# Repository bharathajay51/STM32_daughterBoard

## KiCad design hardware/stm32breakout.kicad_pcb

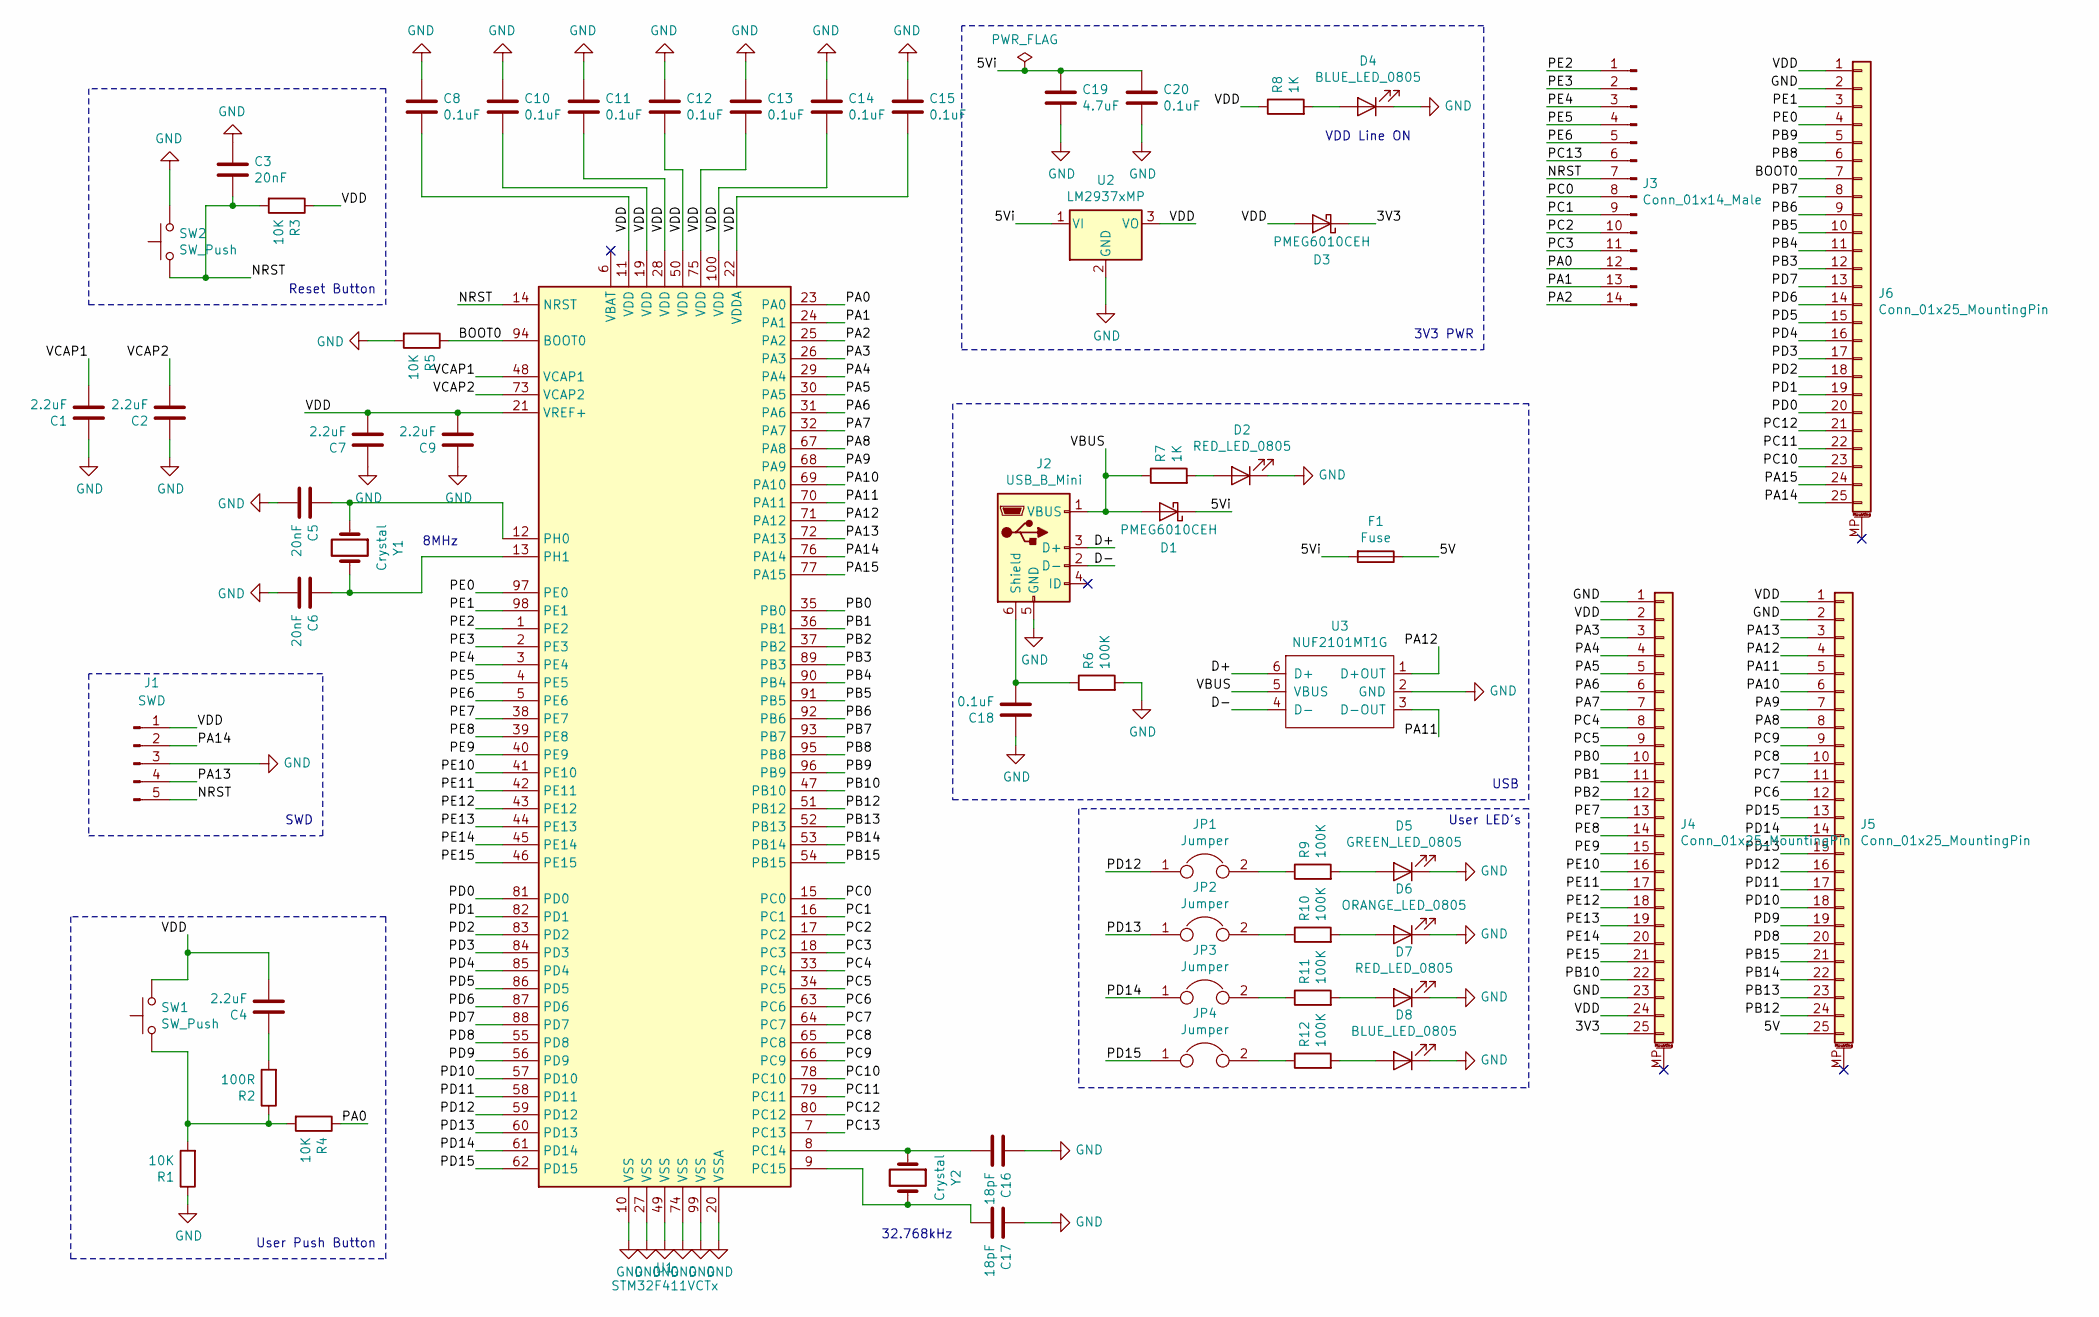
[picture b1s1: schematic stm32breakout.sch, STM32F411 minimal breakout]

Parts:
C1, C2, C4, C7, C9: 2.2uF; C_0805_2012Metric_Pad1.15x1.40mm_HandSolder
C3, C5, C6: 20nF; C_0805_2012Metric_Pad1.15x1.40mm_HandSolder
C8, C10, C11, C12, C13, C14, C15, C18, C20: 0.1uF; C_0805_2012Metric_Pad1.15x1.40mm_HandSolder
C16, C17: 18pF; C_0805_2012Metric_Pad1.15x1.40mm_HandSolder
C19: 4.7uF; C_0805_2012Metric_Pad1.15x1.40mm_HandSolder
D1, D3: PMEG6010CEH; D_SOD-123
D2, D7: RED_LED_0805; LED_0805_2012Metric_Pad1.15x1.40mm_HandSolder
D4, D8: BLUE_LED_0805; LED_0805_2012Metric_Pad1.15x1.40mm_HandSolder
D5: GREEN_LED_0805; LED_0805_2012Metric_Pad1.15x1.40mm_HandSolder
D6: ORANGE_LED_0805; LED_0805_2012Metric_Pad1.15x1.40mm_HandSolder
F1: Fuse; Fuse_1206_3216Metric_Pad1.42x1.75mm_HandSolder
J1: SWD; PinHeader_1x05_P2.54mm_Vertical
J2: USB_B_Mini; USB_Mini-B_Lumberg_2486_01_Horizontal
J3: Conn_01x14_Male; PinHeader_1x14_P2.54mm_Vertical
J4, J5, J6: Conn_01x25_MountingPin; PinHeader_1x25_P2.54mm_Vertical
JP1, JP2, JP3, JP4: Jumper; PinHeader_1x02_P2.54mm_Vertical
R1, R3, R4, R5: 10K; R_0805_2012Metric_Pad1.15x1.40mm_HandSolder
R2: 100R; R_0805_2012Metric_Pad1.15x1.40mm_HandSolder
R6, R9, R10, R11, R12: 100K; R_0805_2012Metric_Pad1.15x1.40mm_HandSolder
R7, R8: 1K; R_0805_2012Metric_Pad1.15x1.40mm_HandSolder
SW1, SW2: SW_Push; SW_PUSH_6mm_H4.3mm
U1: STM32F411VCTx; LQFP-100_14x14mm_P0.5mm
U2: LM2937xMP; SOT-223-3_TabPin2
U3: NUF2101MT1G; TSOP-6_1.65x3.05mm_P0.95mm
Y1: Crystal; Crystal_HC49-4H_Vertical
Y2: Crystal; Crystal_SMD_Abracon_ABS25-4Pin_8.0x3.8mm

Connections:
/3V3: D3.1 (K), J4.25
/5V: F1.1, J5.25
/5Vi: C19.1, C20.1, D1.1 (K), F1.2, U2.1 (VI)
/BOOT0: J6.7, R5.1, U1.94 (BOOT0)
/D+: J2.3 (D+), U3.6 (D+)
/D-: J2.2 (D-), U3.4 (D-)
/NRST: C3.2, J1.5, J3.7, R3.2, SW2.1, U1.14 (NRST)
/PA0: J3.12, R4.1, U1.23 (PA0)
/PA1: J3.13, U1.24 (PA1)
/PA2: J3.14, U1.25 (PA2)
/PA3: J4.3, U1.26 (PA3)
/PA4: J4.4, U1.29 (PA4)
/PA5: J4.5, U1.30 (PA5)
/PA6: J4.6, U1.31 (PA6)
/PA7: J4.7, U1.32 (PA7)
/PA8: J5.8, U1.67 (PA8)
/PA9: J5.7, U1.68 (PA9)
/PA10: J5.6, U1.69 (PA10)
/PA11: J5.5, U1.70 (PA11), U3.3 (D-OUT)
/PA12: J5.4, U1.71 (PA12), U3.1 (D+OUT)
/PA13: J1.4, J5.3, U1.72 (PA13)
/PA14: J1.2, J6.25, U1.76 (PA14)
/PA15: J6.24, U1.77 (PA15)
/PB0: J4.10, U1.35 (PB0)
/PB1: J4.11, U1.36 (PB1)
/PB2: J4.12, U1.37 (PB2)
/PB3: J6.12, U1.89 (PB3)
/PB4: J6.11, U1.90 (PB4)
/PB5: J6.10, U1.91 (PB5)
/PB6: J6.9, U1.92 (PB6)
/PB7: J6.8, U1.93 (PB7)
/PB8: J6.6, U1.95 (PB8)
/PB9: J6.5, U1.96 (PB9)
/PB10: J4.22, U1.47 (PB10)
/PB12: J5.24, U1.51 (PB12)
/PB13: J5.23, U1.52 (PB13)
/PB14: J5.22, U1.53 (PB14)
/PB15: J5.21, U1.54 (PB15)
/PC0: J3.8, U1.15 (PC0)
/PC1: J3.9, U1.16 (PC1)
/PC2: J3.10, U1.17 (PC2)
/PC3: J3.11, U1.18 (PC3)
/PC4: J4.8, U1.33 (PC4)
/PC5: J4.9, U1.34 (PC5)
/PC6: J5.12, U1.63 (PC6)
/PC7: J5.11, U1.64 (PC7)
/PC8: J5.10, U1.65 (PC8)
/PC9: J5.9, U1.66 (PC9)
/PC10: J6.23, U1.78 (PC10)
/PC11: J6.22, U1.79 (PC11)
/PC12: J6.21, U1.80 (PC12)
/PC13: J3.6, U1.7 (PC13)
/PD0: J6.20, U1.81 (PD0)
/PD1: J6.19, U1.82 (PD1)
/PD2: J6.18, U1.83 (PD2)
/PD3: J6.17, U1.84 (PD3)
/PD4: J6.16, U1.85 (PD4)
/PD5: J6.15, U1.86 (PD5)
/PD6: J6.14, U1.87 (PD6)
/PD7: J6.13, U1.88 (PD7)
/PD8: J5.20, U1.55 (PD8)
/PD9: J5.19, U1.56 (PD9)
/PD10: J5.18, U1.57 (PD10)
/PD11: J5.17, U1.58 (PD11)
/PD12: J5.16, JP1.1, U1.59 (PD12)
/PD13: J5.15, JP2.1, U1.60 (PD13)
/PD14: J5.14, JP3.1, U1.61 (PD14)
/PD15: J5.13, JP4.1, U1.62 (PD15)
/PE0: J6.4, U1.97 (PE0)
/PE1: J6.3, U1.98 (PE1)
/PE2: J3.1, U1.1 (PE2)
/PE3: J3.2, U1.2 (PE3)
/PE4: J3.3, U1.3 (PE4)
/PE5: J3.4, U1.4 (PE5)
/PE6: J3.5, U1.5 (PE6)
/PE7: J4.13, U1.38 (PE7)
/PE8: J4.14, U1.39 (PE8)
/PE9: J4.15, U1.40 (PE9)
/PE10: J4.16, U1.41 (PE10)
/PE11: J4.17, U1.42 (PE11)
/PE12: J4.18, U1.43 (PE12)
/PE13: J4.19, U1.44 (PE13)
/PE14: J4.20, U1.45 (PE14)
/PE15: J4.21, U1.46 (PE15)
/VBUS: D1.2 (A), J2.1 (VBUS), R7.1, U3.5 (VBUS)
/VCAP1: C1.2, U1.48 (VCAP1)
/VCAP2: C2.2, U1.73 (VCAP2)
/VDD: C4.2, C7.2, C8.2, C9.2, C10.2, C11.2, C12.2, C13.2, C14.2, C15.2, D3.2 (A), J1.1, J4.2, J4.24, J5.1, J6.1, R3.1, R8.1, SW1.2, U1.11 (VDD), U1.19 (VDD), U1.21 (VREF+), U1.22 (VDDA), U1.28 (VDD), U1.50 (VDD), U1.75 (VDD), U1.100 (VDD), U2.3 (VO)
GND: C1.1, C2.1, C3.1, C5.2, C6.2, C7.1, C8.1, C9.1, C10.1, C11.1, C12.1, C13.1, C14.1, C15.1, C16.1, C17.1, C18.1, C19.2, C20.2, D2.1 (K), D4.1 (K), D5.1 (K), D6.1 (K), D7.1 (K), D8.1 (K), J1.3, J2.5 (GND), J4.1, J4.23, J5.2, J6.2, R1.1, R5.2, R6.2, SW2.2, U1.10 (VSS), U1.20 (VSSA), U1.27 (VSS), U1.49 (VSS), U1.74 (VSS), U1.99 (VSS), U2.2 (GND), U3.2 (GND)
unnamed: C4.1, R2.2
unnamed: C5.1, U1.12 (PH0), Y1.1
unnamed: C6.1, U1.13 (PH1), Y1.2
unnamed: C16.2, U1.8 (PC14), Y2.1
unnamed: C17.2, U1.9 (PC15), Y2.2
unnamed: C18.2, J2.6 (Shield), R6.1
unnamed: D2.2 (A), R7.2
unnamed: D4.2 (A), R8.2
unnamed: D5.2 (A), R9.2
unnamed: D6.2 (A), R10.2
unnamed: D7.2 (A), R11.2
unnamed: D8.2 (A), R12.2
unnamed: JP1.2, R9.1
unnamed: JP2.2, R10.1
unnamed: JP3.2, R11.1
unnamed: JP4.2, R12.1
unnamed: R1.2, R2.1, R4.2, SW1.1

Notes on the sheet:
3V3 PWR
VDD Line ON
USB
SWD
User Push Button
Reset Button
User LED's
8MHz
32.768kHz

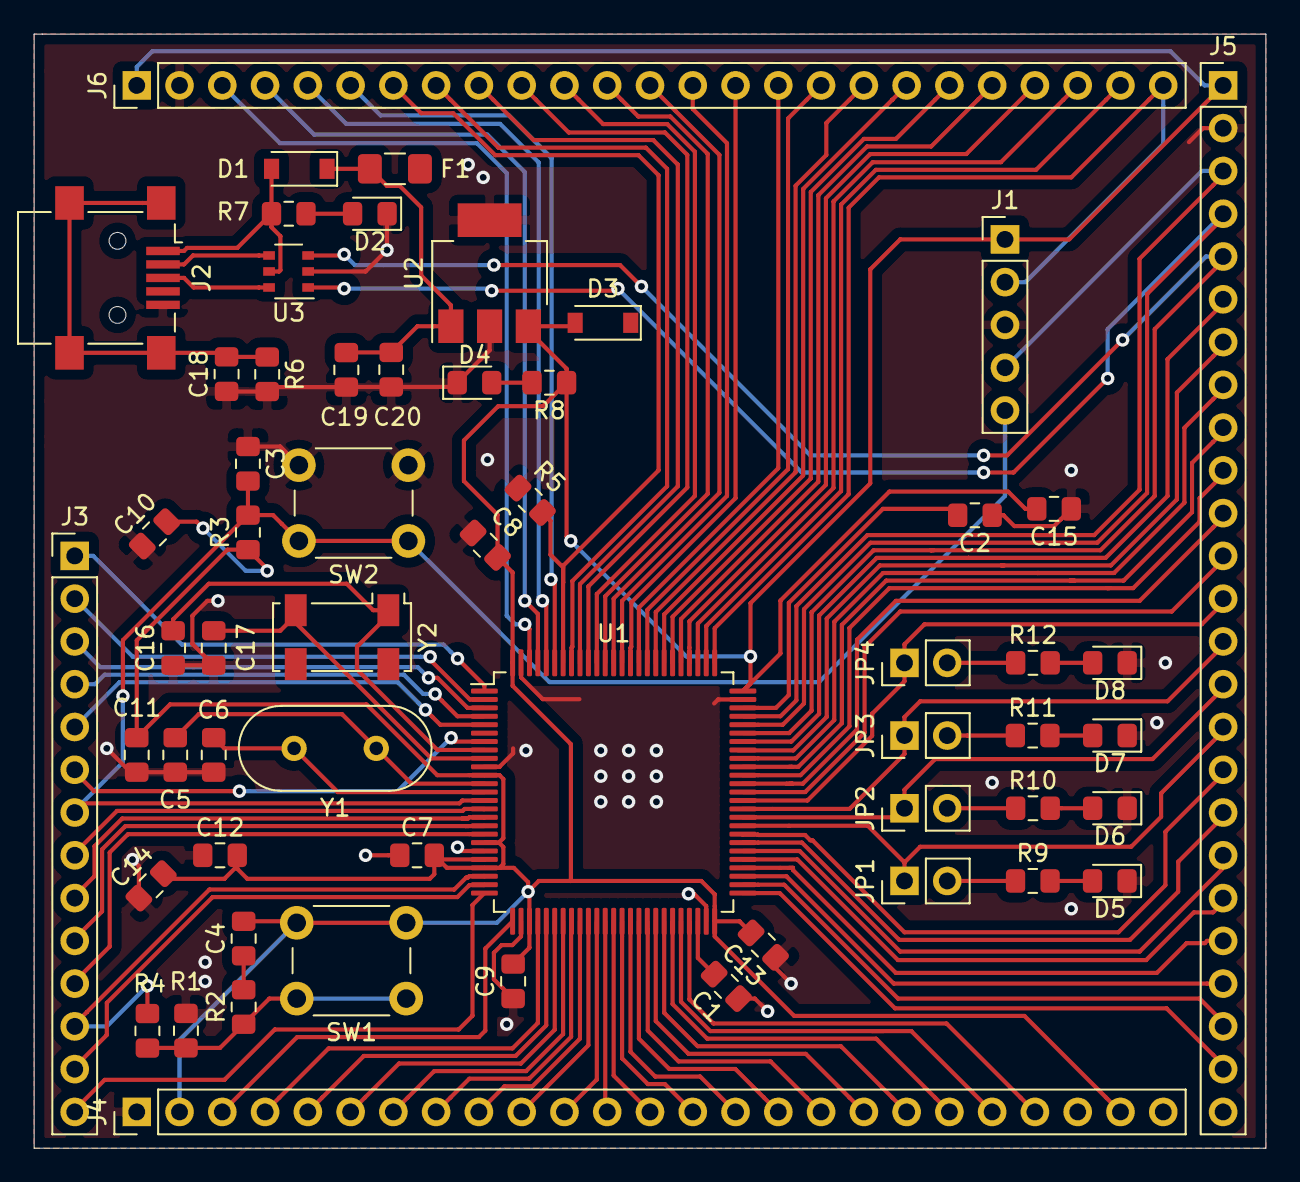
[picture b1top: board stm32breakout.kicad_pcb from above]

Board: 2 copper layers, 73.2 x 66.2 mm, 58 parts (0 on the bottom side), 106 nets.

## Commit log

2020-08-18 Added KiCAD files
